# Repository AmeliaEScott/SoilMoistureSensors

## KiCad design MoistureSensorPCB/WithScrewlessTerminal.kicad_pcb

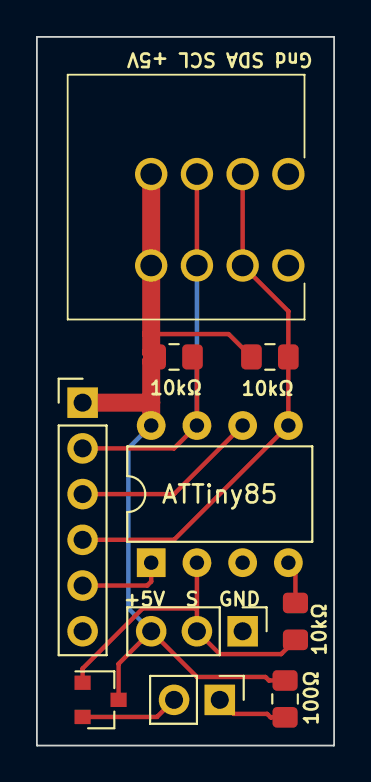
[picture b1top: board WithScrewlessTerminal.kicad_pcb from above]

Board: 2 copper layers, 16.5 x 39.4 mm, 10 parts (0 on the bottom side), 9 nets.

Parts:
I2CConnection1: Conn_01x04; 128340164
I2C_Pullup_SCL1, I2C_Pullup_SDA1: 10k; R_0805_2012Metric_Pad1.15x1.40mm_HandSolder
J1: Conn_01x06_Female; PinHeader_1x06_P2.54mm_Vertical
J2: Conn_01x02; PinHeader_1x02_P2.54mm_Vertical
MCU1: ATtiny85-20PU; DIP-8_W7.62mm
MoistureSensor1: Conn_01x03; PinHeader_1x03_P2.54mm_Vertical
Q1: 2N3904; SOT-23
R3: 10k; R_0805_2012Metric_Pad1.15x1.40mm_HandSolder
R4: 100; R_0805_2012Metric_Pad1.15x1.40mm_HandSolder

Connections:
+5V: I2CConnection1.4, I2C_Pullup_SCL1.1, I2C_Pullup_SDA1.1, J1.1, MCU1.8, MoistureSensor1.3, Q1.3, R4.1
GND: I2CConnection1.1, J1.6, MCU1.4, MoistureSensor1.1, R3.2
unnamed: I2CConnection1.2, I2C_Pullup_SCL1.2, J1.4, MCU1.5
unnamed: I2CConnection1.3, I2C_Pullup_SDA1.2, J1.2, MCU1.7
unnamed: J1.3, MCU1.6
unnamed: J1.5, MCU1.1
unnamed: J2.1, R4.2
unnamed: J2.2, Q1.2
unnamed: MCU1.2, MoistureSensor1.2, Q1.1, R3.1

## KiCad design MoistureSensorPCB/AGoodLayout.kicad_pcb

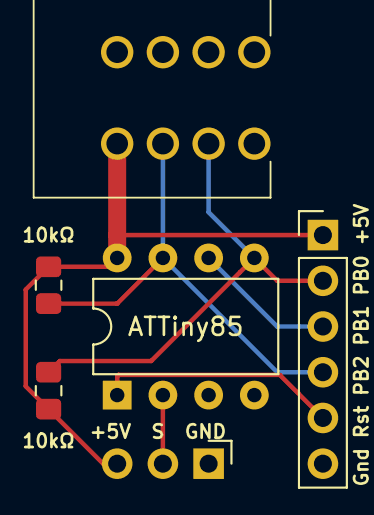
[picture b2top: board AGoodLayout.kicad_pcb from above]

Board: 2 copper layers, 6 parts (0 on the bottom side), 7 nets.

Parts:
I2CConnection1: Conn_01x04; 128340164
I2C_Pullup_SCL1, I2C_Pullup_SDA1: 10k; R_0805_2012Metric_Pad1.15x1.40mm_HandSolder
J1: Conn_01x06_Female; PinHeader_1x06_P2.54mm_Vertical
MCU1: ATtiny85-20PU; DIP-8_W7.62mm
MoistureSensor1: Conn_01x03; PinHeader_1x03_P2.54mm_Horizontal

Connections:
+5V: I2CConnection1.4, I2C_Pullup_SCL1.1, I2C_Pullup_SDA1.1, J1.1, MCU1.8, MoistureSensor1.3
GND: I2CConnection1.1, J1.6, MCU1.4, MoistureSensor1.1
unnamed: I2CConnection1.2, I2C_Pullup_SCL1.2, J1.2, MCU1.5
unnamed: I2CConnection1.3, I2C_Pullup_SDA1.2, J1.4, MCU1.7
unnamed: J1.3, MCU1.6
unnamed: J1.5, MCU1.1
unnamed: MCU1.2, MoistureSensor1.2

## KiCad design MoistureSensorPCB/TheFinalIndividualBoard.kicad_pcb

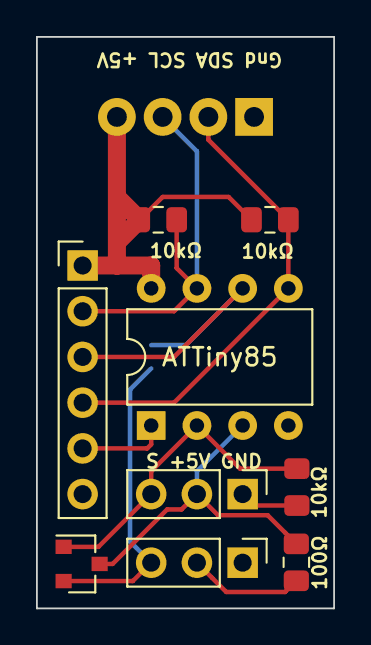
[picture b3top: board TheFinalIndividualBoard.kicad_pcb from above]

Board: 2 copper layers, 16.5 x 31.8 mm, 11 parts (1 on the bottom side), 10 nets.

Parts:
I2CConnection1: Conn_01x04; TerminalBlock_TE_282834-4_1x04_P2.54mm_Horizontal
I2C_Pullup_SCL1, I2C_Pullup_SDA1: 10k; R_0805_2012Metric_Pad1.15x1.40mm_HandSolder
J1: Conn_01x06_Female; PinHeader_1x06_P2.54mm_Vertical
J2: Conn_01x03; PinHeader_1x03_P2.54mm_Vertical
JP1: Jumper_NO_Small; SolderJumper-2_P1.3mm_Open_RoundedPad1.0x1.5mm
MCU1: ATtiny85-20PU; DIP-8_W7.62mm
MoistureSensor1: Conn_01x03; PinHeader_1x03_P2.54mm_Vertical
Q1: 2N3904; SOT-23
R3: 10k; R_0805_2012Metric_Pad1.15x1.40mm_HandSolder
R4: 100; R_0805_2012Metric_Pad1.15x1.40mm_HandSolder

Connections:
+5V: I2CConnection1.4, I2C_Pullup_SCL1.1, I2C_Pullup_SDA1.1, J1.1, MCU1.8
GND: I2CConnection1.1, J1.6, J2.1, MCU1.4, MoistureSensor1.1, R3.2
unnamed: I2CConnection1.2, I2C_Pullup_SCL1.2, J1.4, MCU1.5
unnamed: I2CConnection1.3, I2C_Pullup_SDA1.2, J1.2, MCU1.7
unnamed: J1.3, JP1.2, MCU1.6
unnamed: J1.5, MCU1.1
unnamed: J2.2, R4.2
unnamed: J2.3, JP1.1, Q1.2
unnamed: MCU1.2, MoistureSensor1.3, Q1.1, R3.1
unnamed: MCU1.3, MoistureSensor1.2, Q1.3, R4.1
